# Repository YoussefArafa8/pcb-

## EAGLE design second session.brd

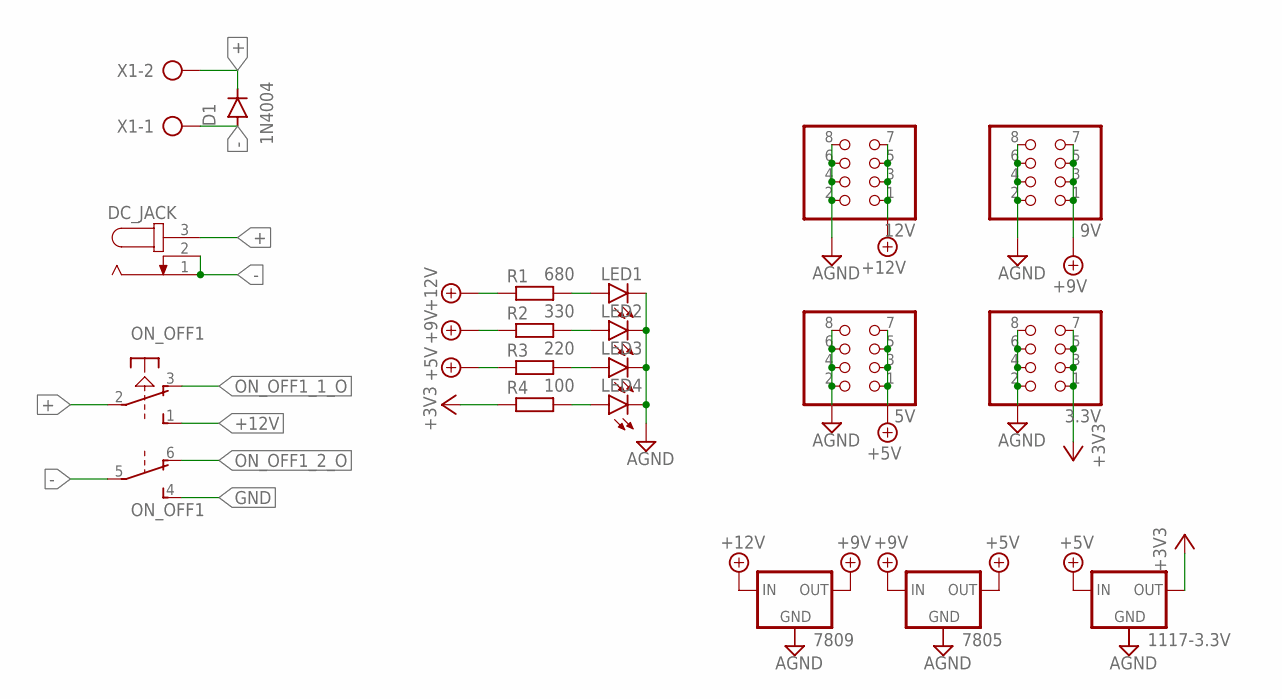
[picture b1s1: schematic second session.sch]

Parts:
3.3V, 5V, 9V, 12V: PINHD-2X4; 2X04
1117-3.3V, 7805, 7809: 78XXS
D1: 1N4004; DO41-10
DC_JACK: JACK-PLUG0; SPC4077
LED1, LED2, LED3, LED4: LED5MM
ON_OFF1: PVA2R
R1: 680; 0207/10
R2: 330; 0207/10
R3: 220; 0207/10
R4: 100; 0207/10
X1: AK500/2-H

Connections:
+: D1.C, DC_JACK.3, ON_OFF1.2, X1.2
+3V3: 3.3V.1, 3.3V.3, 3.3V.5, 3.3V.7, 1117-3.3V.OUT, R4.1
+5V: 5V.1, 5V.3, 5V.5, 5V.7, 1117-3.3V.IN, 7805.OUT, R3.1
+9V: 9V.1, 9V.3, 9V.5, 9V.7, 7805.IN, 7809.OUT, R2.1
+12V: 12V.1, 12V.3, 12V.5, 12V.7, 7809.IN, ON_OFF1.1 (S), R1.1
-: D1.A, DC_JACK.1, DC_JACK.2, ON_OFF1.5, X1.1
AGND: 3.3V.2, 3.3V.4, 3.3V.6, 3.3V.8, 5V.2, 5V.4, 5V.6, 5V.8, 9V.2, 9V.4, 9V.6, 9V.8, 12V.2, 12V.4, 12V.6, 12V.8, LED1.K (C), LED2.K (C), LED3.K (C), LED4.K (C)
GND: ON_OFF1.4 (S)
unnamed: LED1.A, R1.2
unnamed: LED2.A, R2.2
unnamed: LED3.A, R3.2
unnamed: LED4.A, R4.2
ON_OFF1_1_O: ON_OFF1.3 (O)
ON_OFF1_2_O: ON_OFF1.6 (O)

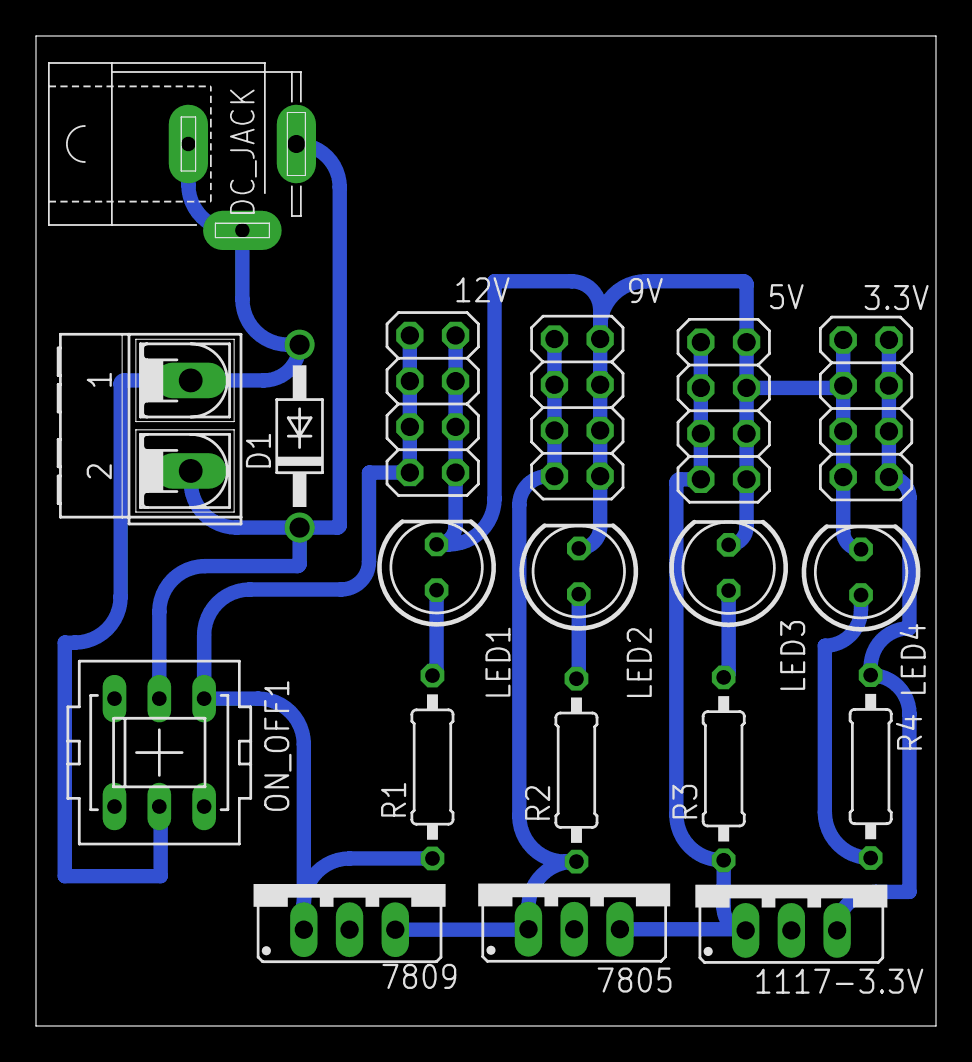
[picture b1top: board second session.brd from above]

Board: 2 copper layers, 50.0 x 55.0 mm, 19 parts (0 on the bottom side), 11 nets.

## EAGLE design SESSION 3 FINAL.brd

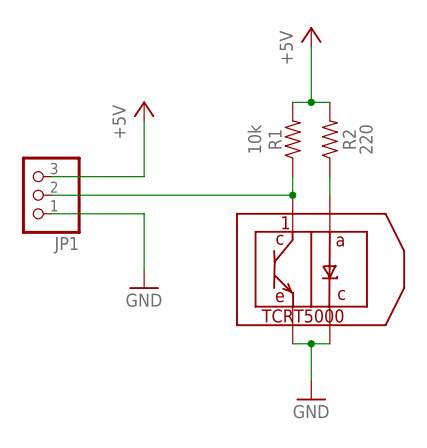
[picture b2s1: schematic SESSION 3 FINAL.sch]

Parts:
1: TCRT5000; 5000
JP1: PINHD-1X3; 1X03
R1: 10k; AXIAL-0.3
R2: 220; AXIAL-0.3

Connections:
+5V: JP1.3, R1.P$2 (2), R2.P$2 (2)
GND: 1.P$2, 1.P$4, JP1.1
unnamed: 1.P$1, JP1.2, R1.P$1 (1)
unnamed: 1.P$3, R2.P$1 (1)

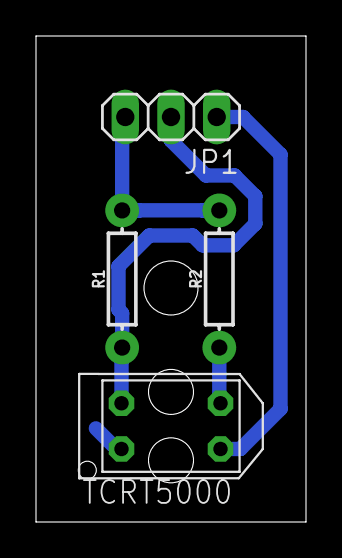
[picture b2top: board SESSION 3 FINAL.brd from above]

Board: 2 copper layers, 15.0 x 27.0 mm, 4 parts (0 on the bottom side), 4 nets.

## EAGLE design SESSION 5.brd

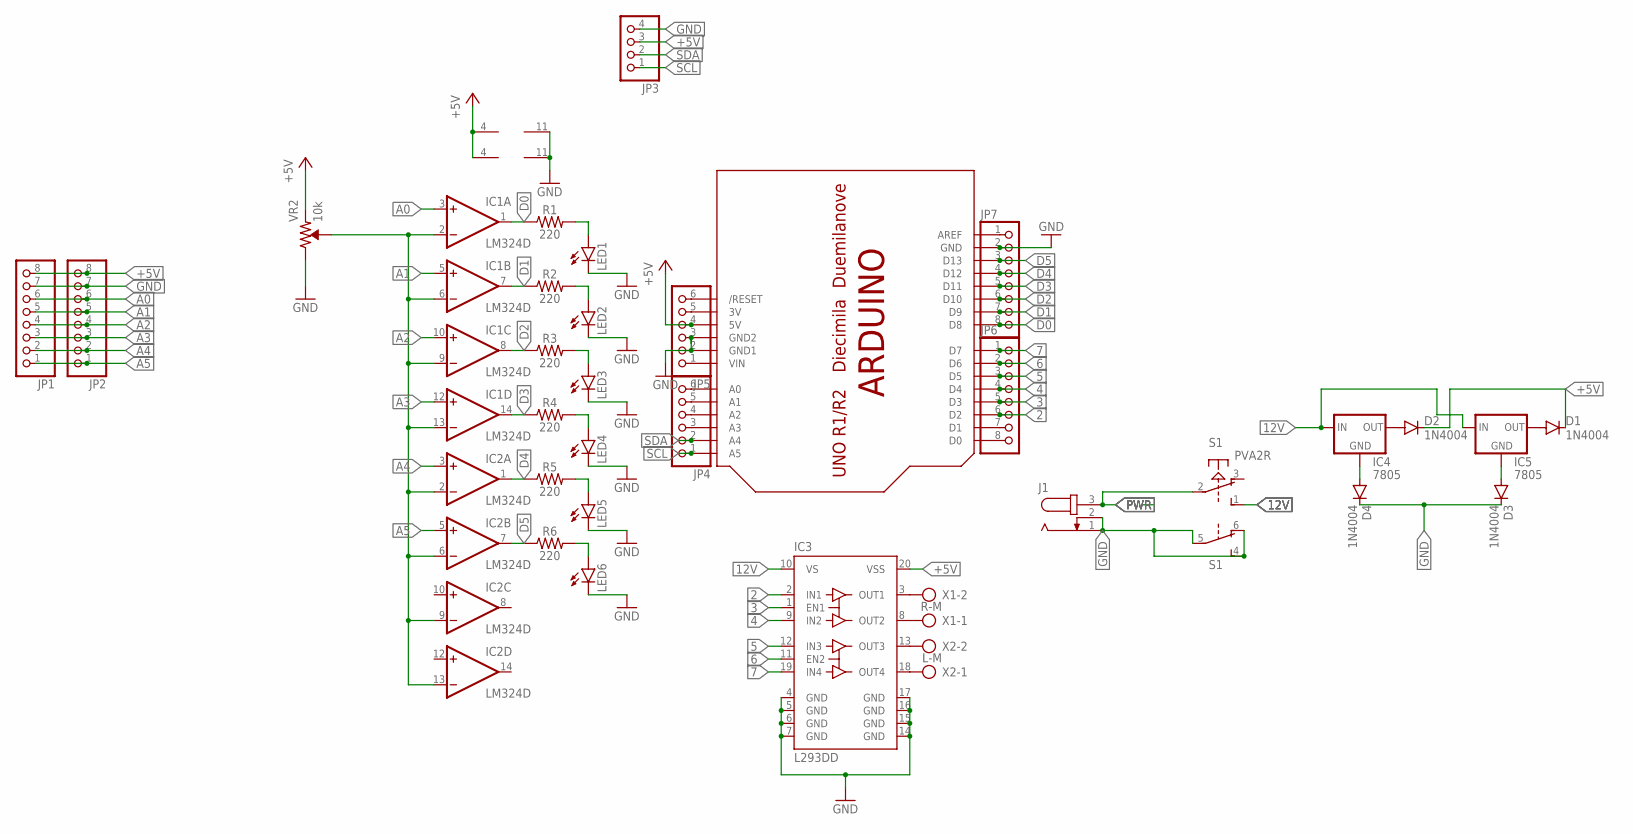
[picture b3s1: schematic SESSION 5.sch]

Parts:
D1, D2, D3, D4: 1N4004; DO41-10
IC1, IC2: LM324D; SO14
IC3: L293DD; SO20
IC4, IC5: 7805; 78XXS
J1: JACK-PLUG1; SPC4078
JP1, JP2, JP6, JP7: PINHD-1X8; 1X08
JP3: PINHD-1X4; 1X04
JP4, JP5: PINHD-1X6; 1X06
LED1, LED2, LED3, LED4, LED5, LED6: LEDCHIPLED_0805; CHIPLED_0805
R1, R2, R3, R4, R5, R6: 220; 1206
S1: PVA2R
U$1: ARDUINO-NODIM
VR2: 10k; TRIMPOT-PTH-3386U
X1: R-M; AK500/2-H
X2: L-M; AK500/2-H

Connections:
2: IC3.2 (IN1), JP6.6, U$1.D2
3: IC3.1 (EN1), JP6.5, U$1.D3
4: IC3.9 (IN2), JP6.4, U$1.D4
5: IC3.12 (IN3), JP6.3, U$1.D5
6: IC3.11 (EN2), JP6.2, U$1.D6
7: IC3.19 (IN4), JP6.1, U$1.D7
12V: IC3.10 (VS), IC4.IN, IC5.IN, S1.1 (S)
+5V: D1.C, D2.C, IC1.4 (V+), IC2.4 (V+), IC3.20 (VSS), JP1.8, JP2.8, JP3.3, JP5.4, U$1.5V, VR2.1 (CCW)
A0: IC1.3 (+IN), JP1.6, JP2.6
A1: IC1.5 (+IN), JP1.5, JP2.5
A2: IC1.10 (+IN), JP1.4, JP2.4
A3: IC1.12 (+IN), JP1.3, JP2.3
A4: IC2.3 (+IN), JP1.2, JP2.2
A5: IC2.5 (+IN), JP1.1, JP2.1
D0: IC1.1 (OUT), JP7.8, R1.1, U$1.D8
D1: IC1.7 (OUT), JP7.7, R2.1, U$1.D9
D2: IC1.8 (OUT), JP7.6, R3.1, U$1.D10
D3: IC1.14 (OUT), JP7.5, R4.1, U$1.D11
D4: IC2.1 (OUT), JP7.4, R5.1, U$1.D12
D5: IC2.7 (OUT), JP7.3, R6.1, U$1.D13
GND: D3.C, D4.C, IC1.11 (V-), IC2.11 (V-), IC3.4 (GND), IC3.5 (GND), IC3.6 (GND), IC3.7 (GND), IC3.14 (GND), IC3.15 (GND), IC3.16 (GND), IC3.17 (GND), J1.1, J1.2, JP1.7, JP2.7, JP3.4, JP5.2, JP5.3, JP7.2, LED1.C, LED2.C, LED3.C, LED4.C, LED5.C, LED6.C, S1.4 (S), S1.5, S1.6 (O), U$1.GND, U$1.GND1, U$1.GND2, VR2.3 (CW)
unnamed: LED1.A, R1.2
unnamed: IC3.8 (OUT2), X1.1
unnamed: IC3.3 (OUT1), X1.2
unnamed: LED2.A, R2.2
unnamed: IC3.18 (OUT4), X2.1
unnamed: LED3.A, R3.2
unnamed: IC3.13 (OUT3), X2.2
unnamed: LED4.A, R4.2
unnamed: LED5.A, R5.2
unnamed: D1.A, IC5.OUT
unnamed: LED6.A, R6.2
unnamed: D2.A, IC4.OUT
unnamed: D4.A, IC4.GND
unnamed: IC1.2 (-IN), IC1.6 (-IN), IC1.9 (-IN), IC1.13 (-IN), IC2.2 (-IN), IC2.6 (-IN), IC2.9 (-IN), IC2.13 (-IN), VR2.2 (WIPER)
unnamed: D3.A, IC5.GND
unnamed: JP4.3, U$1.A3
unnamed: JP4.4, U$1.A2
unnamed: JP4.5, U$1.A1
unnamed: JP4.6, U$1.A0
unnamed: JP5.1, U$1.VIN
unnamed: JP5.5, U$1.3V
unnamed: JP5.6, U$1.RESET (/RESET)
unnamed: JP6.7, U$1.D1
unnamed: JP6.8, U$1.D0
unnamed: JP7.1, U$1.AREF
PWR: J1.3, S1.2
SCL: JP3.1, JP4.1, U$1.A5
SDA: JP3.2, JP4.2, U$1.A4

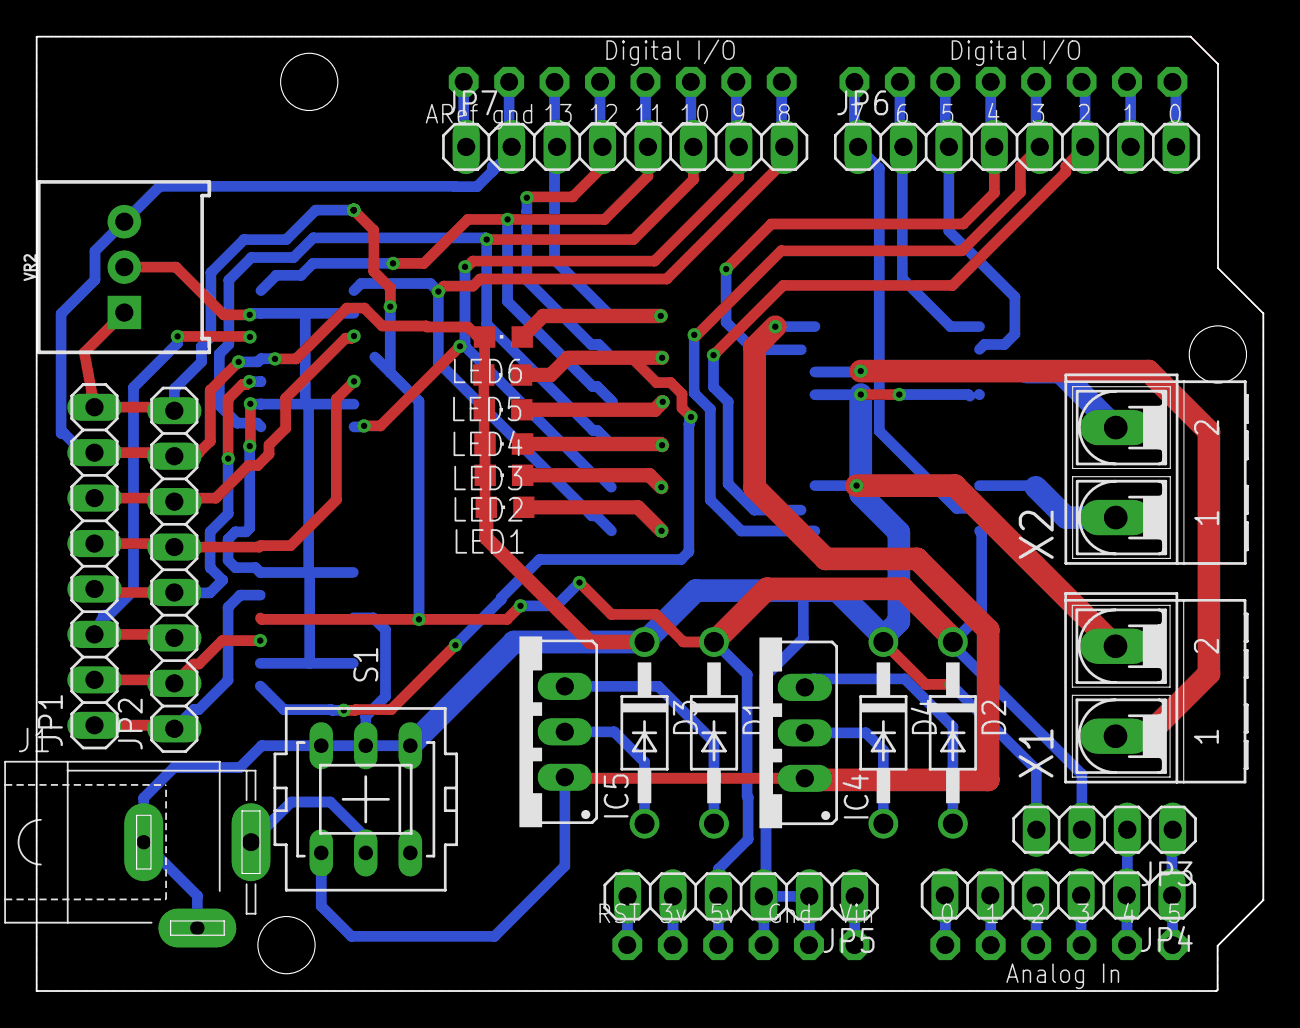
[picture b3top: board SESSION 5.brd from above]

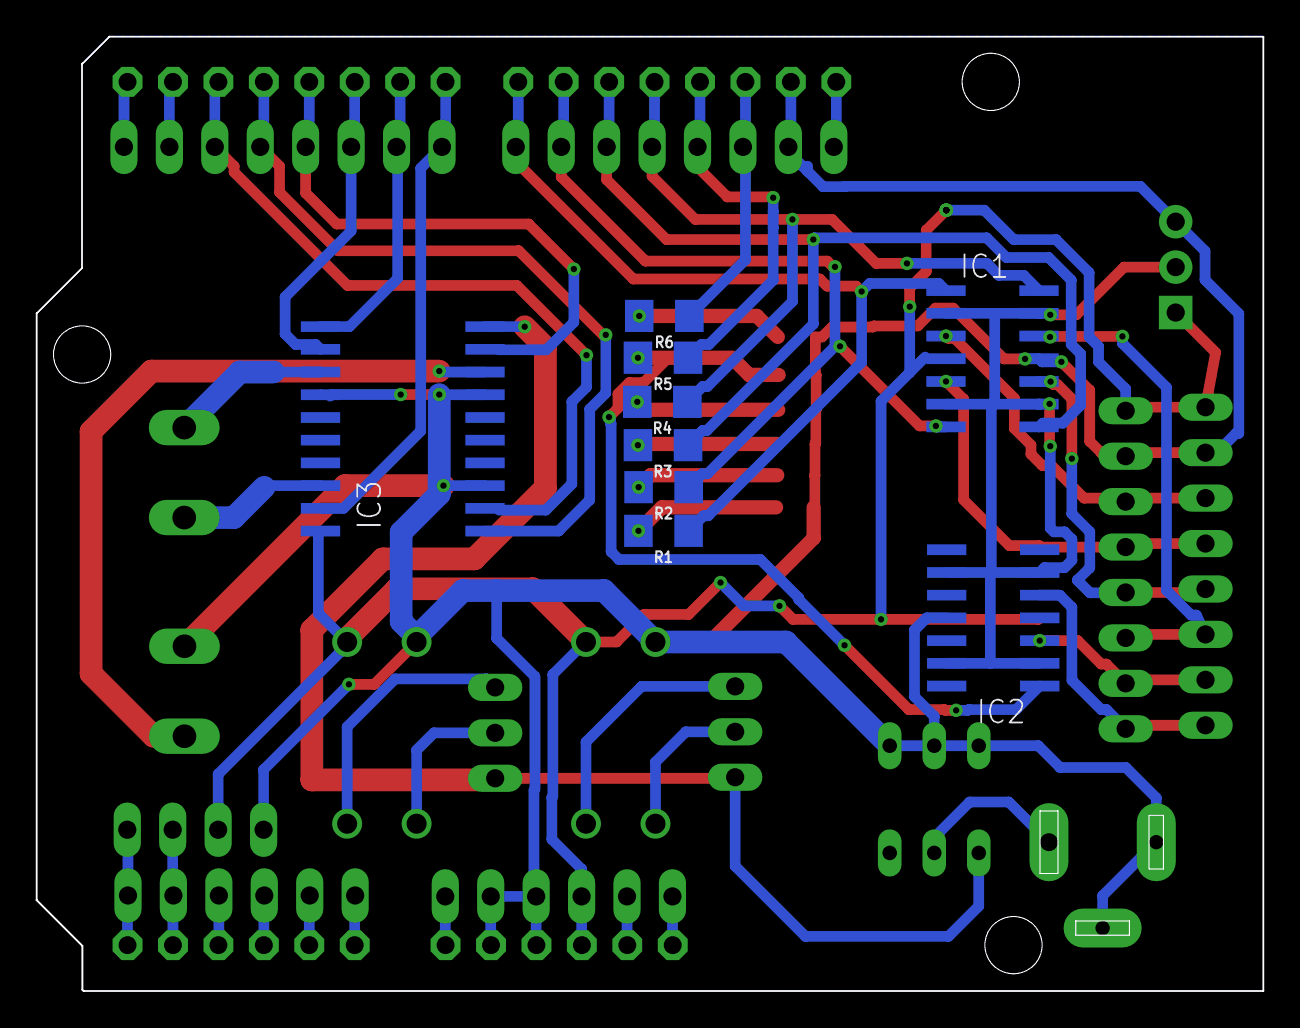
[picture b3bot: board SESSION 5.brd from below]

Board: 2 copper layers, 68.6 x 53.4 mm, 34 parts (9 on the bottom side), 49 nets.

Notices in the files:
parts and their libraries:
SparkFun-Resistors: Licensing: Creative Commons ShareAlike 4.0 International - https://creativecommons.org/licenses/by-sa/4.0
